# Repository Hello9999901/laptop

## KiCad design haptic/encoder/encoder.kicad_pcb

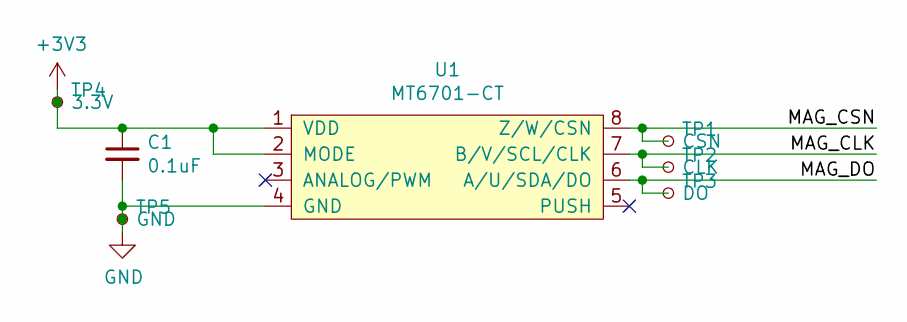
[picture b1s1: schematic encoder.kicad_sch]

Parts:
C1: 0.1uF; C_0603_1608Metric; LCSC C1591
TP1: CSN; TestPoint_THTPad_D1.0mm_Drill0.5mm
TP2: CLK; TestPoint_THTPad_D1.0mm_Drill0.5mm
TP3: DO; TestPoint_THTPad_D1.0mm_Drill0.5mm
TP4: 3.3V; TestPoint_THTPad_D1.0mm_Drill0.5mm
TP5: GND; TestPoint_THTPad_D1.0mm_Drill0.5mm
U1: MT6701-CT; SOIC-8_3.9x4.9mm_P1.27mm; LCSC C2856764, or C3003196

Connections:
+3V3: C1.1, TP4.1, U1.1 (VDD), U1.2 (MODE)
/MAG_CLK: TP2.1, U1.7 (B/V/SCL/CLK)
/MAG_CSN: TP1.1, U1.8 (Z/W/CSN)
/MAG_DO: TP3.1, U1.6 (A/U/SDA/DO)
GND: C1.2, TP5.1, U1.4 (GND)

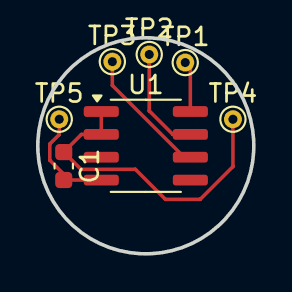
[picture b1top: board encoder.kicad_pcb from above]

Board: 2 copper layers, 12.0 x 12.0 mm, 7 parts (0 on the bottom side), 5 nets.
